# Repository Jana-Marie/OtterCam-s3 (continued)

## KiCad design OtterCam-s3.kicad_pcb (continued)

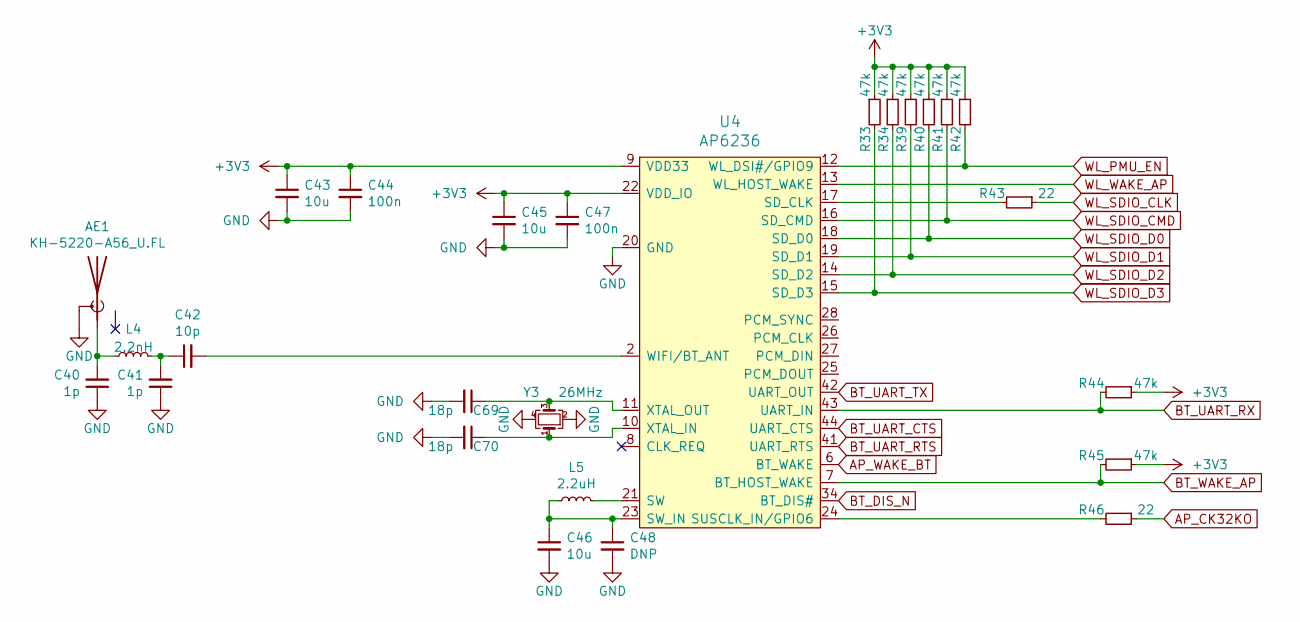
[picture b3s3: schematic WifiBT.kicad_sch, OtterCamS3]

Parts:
AE1: KH-5220-A56_U.FL; U.FL_Hirose_U.FL-R-SMT-1_Vertical
C40, C41: 1p; C_0402
C42: 10p; C_0402
C43, C45, C46: 10u; C_0603
C44, C47: 100n; C_0402
C48: DNP; C_0402
C69, C70: 18p; C_0402
L4: 2.2nH; L_0402
L5: 2.2uH; L_Taiyo-Yuden_MD-3030; LCSC C167747
R33, R34, R39, R40, R41, R42, R44, R45: 47k; R_0402
R43, R46: 22; R_0402
U4: AP6236; LGA_44_12x12mm_0.9mm
Y3: 26MHz; Oscillator_3225

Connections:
+3V3: C43.1, C44.1, C45.1, C47.1, R33.1, R34.1, R39.1, R40.1, R41.1, R42.1, R44.1, R45.1, U4.9 (VDD33), U4.22 (VDD_IO); also elsewhere on the board
AP_CK32KO: R46.1; also elsewhere on the board
AP_WAKE_BT: U4.6 (BT_WAKE); also elsewhere on the board
BT_DIS_N: U4.34 (BT_DIS#); also elsewhere on the board
BT_UART_CTS: U4.44 (UART_CTS); also elsewhere on the board
BT_UART_RTS: U4.41 (UART_RTS); also elsewhere on the board
BT_UART_RX: R44.2, U4.43 (UART_IN); also elsewhere on the board
BT_UART_TX: U4.42 (UART_OUT); also elsewhere on the board
BT_WAKE_AP: R45.2, U4.7 (BT_HOST_WAKE); also elsewhere on the board
GND: AE1.2 (Shield), C40.1, C41.1, C43.2, C44.2, C45.2, C46.2, C47.2, C48.2, C69.2, C70.2, U4.1 (GND), U4.20 (GND), U4.31 (GND), U4.33 (GND), U4.36 (GND), Y3.2, Y3.4; also elsewhere on the board
unnamed: AE1.1 (A), C40.2, L4.1
unnamed: C41.2, C42.1, L4.2
unnamed: C42.2, U4.2 (WIFI/BT_ANT)
unnamed: C46.1, C48.1, L5.1, U4.23 (SW_IN)
unnamed: C69.1, U4.11 (XTAL_OUT), Y3.3
unnamed: C70.1, U4.10 (XTAL_IN), Y3.1
unnamed: L5.2, U4.21 (SW)
unnamed: R43.2, U4.17 (SD_CLK)
unnamed: R46.2, U4.24 (SUSCLK_IN/GPIO6)
WL_PMU_EN: R42.2, U4.12 (WL_DSI#/GPIO9); also elsewhere on the board
WL_SDIO_CLK: R43.1; also elsewhere on the board
WL_SDIO_CMD: R41.2, U4.16 (SD_CMD); also elsewhere on the board
WL_SDIO_D0: R40.2, U4.18 (SD_D0); also elsewhere on the board
WL_SDIO_D1: R39.2, U4.19 (SD_D1); also elsewhere on the board
WL_SDIO_D2: R34.2, U4.14 (SD_D2); also elsewhere on the board
WL_SDIO_D3: R33.2, U4.15 (SD_D3); also elsewhere on the board
WL_WAKE_AP: U4.13 (WL_HOST_WAKE); also elsewhere on the board

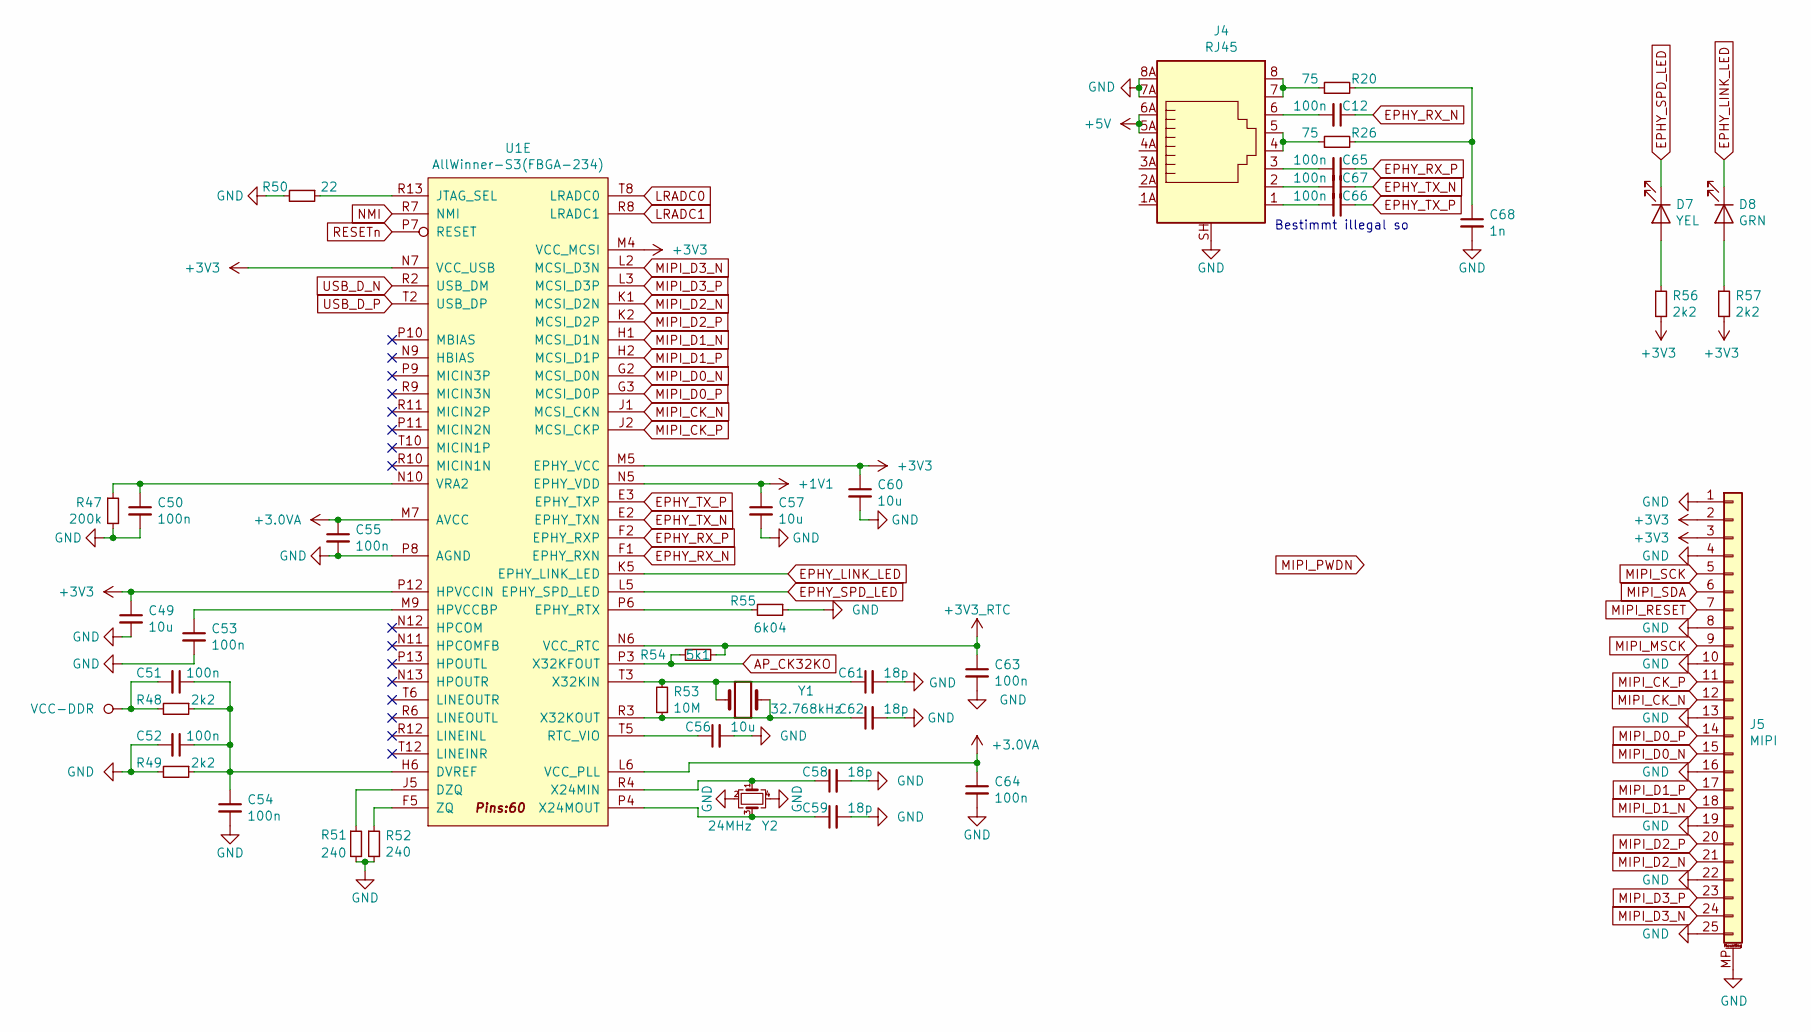
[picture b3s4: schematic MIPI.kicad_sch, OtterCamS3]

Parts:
C12, C65, C66, C67: 100n; C_0805
C49, C56, C57, C60: 10u; C_0603
C50, C51, C52, C53, C54, C55, C63, C64: 100n; C_0402
C58, C59, C61, C62: 18p; C_0402
C68: 1n; C_0805
D7: YEL; LED_0603_1608Metric_Castellated
D8: GRN; LED_0603_1608Metric_Castellated
J4: RJ45; 1-338088-3
J5: MIPI; FH35C-25S
R20, R26: 75; R_0402
R47: 200k; R_0402
R48, R49, R56, R57: 2k2; R_0402
R50: 22; R_0402
R51, R52: 240; R_0402
R53: 10M; R_0402
R54: 5k1; R_0402
R55: 6k04; R_0402
U1: AllWinner-S3(FBGA-234); FBGA-234(Pitch-0.65mm_Pad-0.3mm_11x11x1.08mm)
Y1: 32.768kHz; Crystal_SMD_3215-2Pin_3.2x1.5mm
Y2: 24MHz; Oscillator_3225

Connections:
+1V1: C57.1, U1.N5 (EPHY_VDD); also elsewhere on the board
+3.0VA: C55.1, C64.1, U1.L6 (VCC_PLL), U1.M7 (AVCC); also elsewhere on the board
+3.3V_RTC: C63.1, R54.2, U1.N6 (VCC_RTC); also elsewhere on the board
+3V3: C49.1, C60.1, J5.2, J5.3, R56.2, R57.2, U1.M4 (VCC_MCSI), U1.M5 (EPHY_VCC), U1.N7 (VCC_USB), U1.P12 (HPVCCIN); also elsewhere on the board
+5V: J4.5A, J4.6A; also elsewhere on the board
AP_CK32KO: R54.1, U1.P3 (X32KFOUT); also elsewhere on the board
EPHY_LINK_LED: D8.1 (K), U1.K5 (EPHY_LINK_LED)
EPHY_RX_N: C12.1, U1.F1 (EPHY_RXN)
EPHY_RX_P: C65.1, U1.F2 (EPHY_RXP)
EPHY_SPD_LED: D7.1 (K), U1.L5 (EPHY_SPD_LED)
EPHY_TX_N: C67.1, U1.E2 (EPHY_TXN)
EPHY_TX_P: C66.1, U1.E3 (EPHY_TXP)
GND: C49.2, C50.2, C52.2, C53.2, C54.2, C55.2, C56.2, C57.2, C58.2, C59.2, C60.2, C61.2, C62.2, C63.2, C64.2, C68.2, J4.7A, J4.8A, J4.SH, J5.1, J5.4, J5.8, J5.10, J5.13, J5.16, J5.19, J5.22, J5.25, J5.MP (MountPin), R47.2, R49.2, R50.2, R51.2, R52.2, R55.1, U1.P8 (AGND), Y2.2, Y2.4; also elsewhere on the board
LRADC0: U1.T8 (LRADC0)
LRADC1: U1.R8 (LRADC1)
MIPI_CK_N: J5.12, U1.J1 (MCSI_CKN)
MIPI_CK_P: J5.11, U1.J2 (MCSI_CKP)
MIPI_D0_N: J5.15, U1.G2 (MCSI_D0N)
MIPI_D0_P: J5.14, U1.G3 (MCSI_D0P)
MIPI_D1_N: J5.18, U1.H1 (MCSI_D1N)
MIPI_D1_P: J5.17, U1.H2 (MCSI_D1P)
MIPI_D2_N: J5.21, U1.K1 (MCSI_D2N)
MIPI_D2_P: J5.20, U1.K2 (MCSI_D2P)
MIPI_D3_N: J5.24, U1.L2 (MCSI_D3N)
MIPI_D3_P: J5.23, U1.L3 (MCSI_D3P)
MIPI_MSCK: J5.9; also elsewhere on the board
MIPI_RESET: J5.7; also elsewhere on the board
MIPI_SCK: J5.5; also elsewhere on the board
MIPI_SDA: J5.6; also elsewhere on the board
NMI: U1.R7 (NMI)
unnamed: C12.2, J4.6
unnamed: C50.1, R47.1, U1.N10 (VRA2)
unnamed: C51.1, C52.1, C54.1, R48.1, R49.1, U1.H6 (DVREF)
unnamed: C53.1, U1.M9 (HPVCCBP)
unnamed: C56.1, U1.T5 (RTC_VIO)
unnamed: C58.1, U1.R4 (X24MIN), Y2.1
unnamed: C59.1, U1.P4 (X24MOUT), Y2.3
unnamed: C61.1, R53.2, U1.T3 (X32KIN), Y1.1
unnamed: C62.1, R53.1, U1.R3 (X32KOUT), Y1.2
unnamed: C65.2, J4.3
unnamed: C66.2, J4.1
unnamed: C67.2, J4.2
unnamed: C68.1, R20.2, R26.2
unnamed: D7.2 (A), R56.1
unnamed: D8.2 (A), R57.1
unnamed: J4.4, J4.5, R26.1
unnamed: J4.7, J4.8, R20.1
unnamed: R50.1, U1.R13 (JTAG_SEL)
unnamed: R51.1, U1.J5 (DZQ)
unnamed: R52.1, U1.F5 (ZQ)
unnamed: R55.2, U1.P6 (EPHY_RTX)
RESETn: U1.P7 (RESET); also elsewhere on the board
USB_D_N: U1.R2 (USB_DM); also elsewhere on the board
USB_D_P: U1.T2 (USB_DP); also elsewhere on the board
VCC-DDR: C51.2, R48.2; also elsewhere on the board

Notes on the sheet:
Bestimmt illegal so

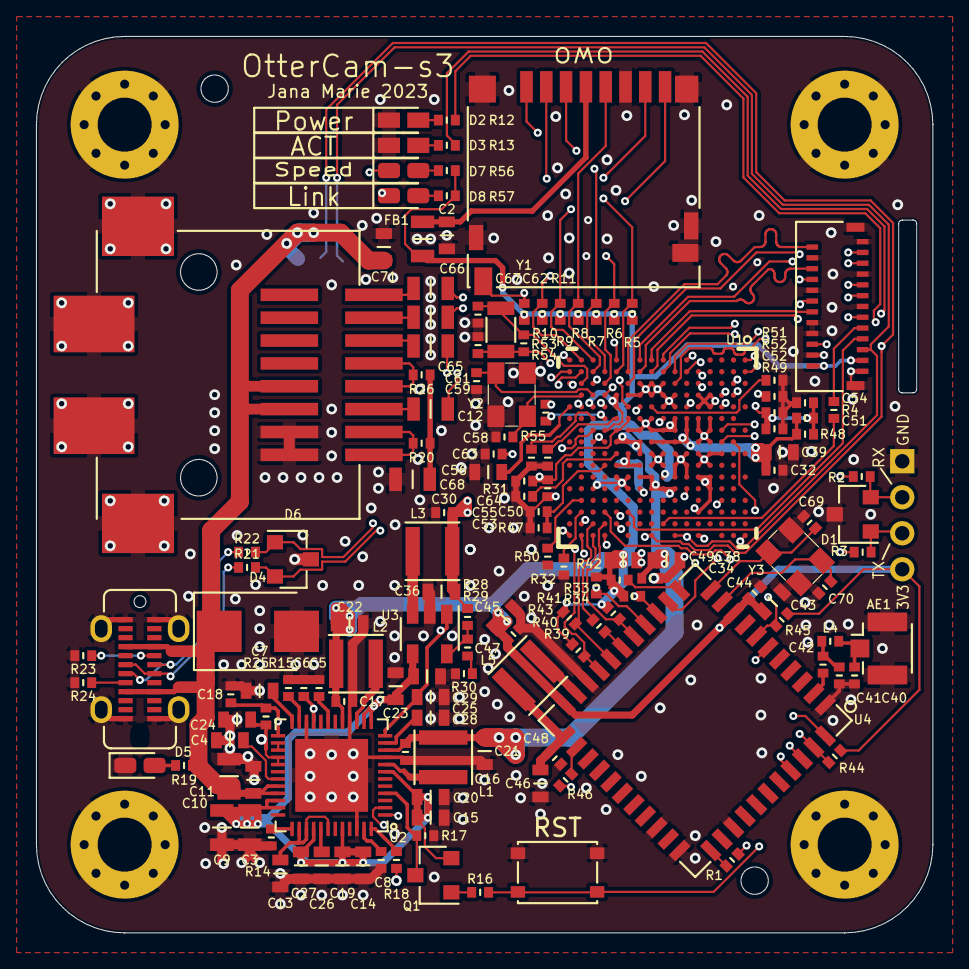
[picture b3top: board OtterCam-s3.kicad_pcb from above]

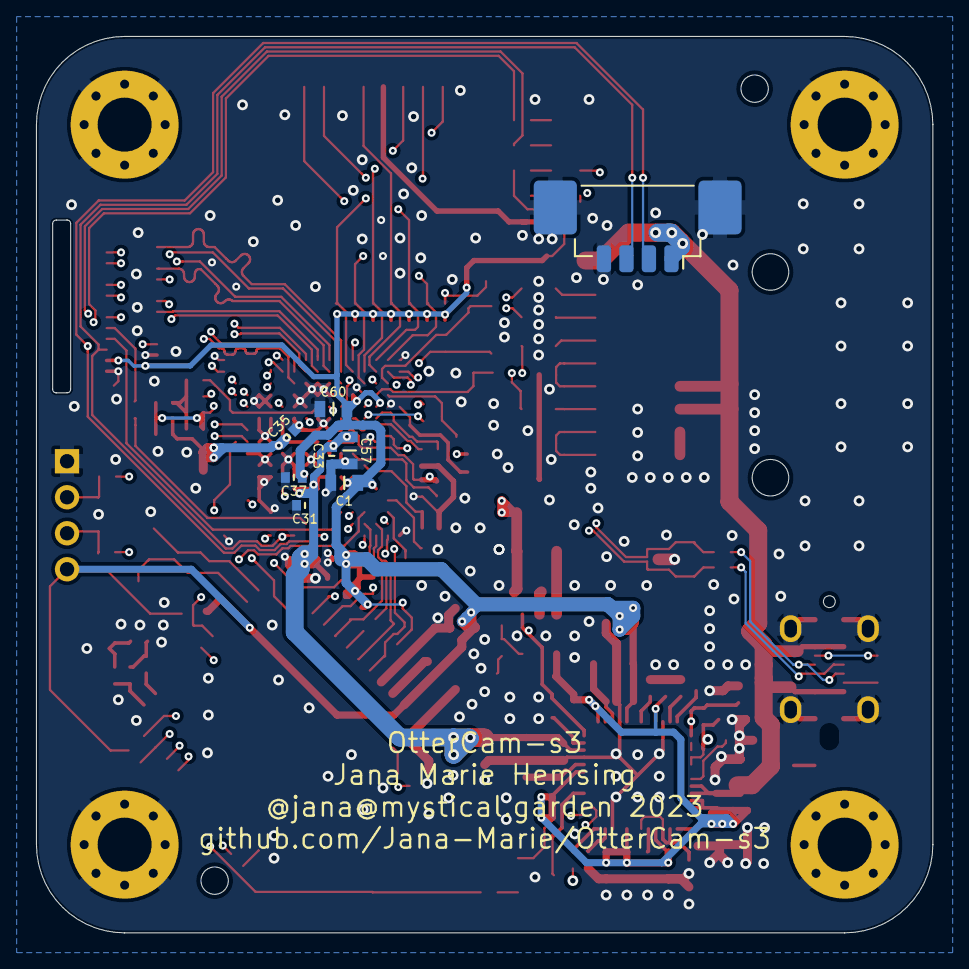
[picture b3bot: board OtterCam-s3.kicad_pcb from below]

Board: 4 copper layers, 49.8 x 49.8 mm, 159 parts (12 on the bottom side), 121 nets.

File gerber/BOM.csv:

Comment,Designator,Footprint,LCSC,
KH-5220-A56_U.FL,AE1,Connector_Coaxial:U.FL_Hirose_U.FL-R-SMT-1_Vertical,,
47u,"C10,C9,C3",otter:C_0805,C76636,
470n,C18,otter:C_0402,C47339,
10u,"C2,C1,C71,C15,C14,C21,C22,C20,C19,C23,C24,C25,C26,C27,C28,C4,C38,C39,C29,C36,C13,C11,C45,C43,C46,C57,C60,C56,C49",otter:C_0603,C19702 ,
100n,"C35,C37,C33,C34,C31,C32,C30,C5,C6,C17,C16,C47,C44,C55,C64,C63,C54,C51,C53,C52,C50",otter:C_0402,C1525,
1p,"C41,C40",otter:C_0402,C1550,
10p,C42,otter:C_0402,C32949,
DNP,C48,otter:C_0402,DNP,
100n,"C66,C67,C65,C12",otter:C_0805,C49678 ,
1n,C68,otter:C_0805,C46653,
2.2u,C7,otter:C_0603,C23630,
18p,"C70,C69,C58,C59,C61,C62",otter:C_0402,C1549,
1n,C8,otter:C_0402,C1523,
ESD5302F,"D1,D6",Package_TO_SOT_SMD:SOT-23,C32677,C239643
LED,D3,otter:LED_0603_1608Metric,C2286,
P6SMB6.8CA,D4,Diode_SMD:D_SMB,C78395,
LED,D5,LED_SMD:LED_0603_1608Metric_Castellated,C72043,
YEL,D7,LED_SMD:LED_0603_1608Metric_Castellated,C72038,
GRN,"D2,D8",LED_SMD:LED_0603_1608Metric_Castellated,C72043,
FERRET,FB1,otter:R_0805,C1017,
Fiducial,"FID1,FID2",otter:FID_1.52,DNP,
M3,"H1,H2,H3,H4",MountingHole:MountingHole_3mm_Pad_Via,DNP,
UART,J1,otter:PinHeader_1x04_P2.00mm_Vertical_nosilk_center,DNP,
SD,J2,Connector_Card:microSD_HC_Hirose_DM3D-SF,DNP,
USB,J3,otter:918-418K2022Y40004,DNP,
RJ45,J4,otter:1-338088-3,DNP,
MIPI,J5,otter:FH35C-25S,DNP,
LENS,J6,Connector_Molex:Molex_PicoBlade_53398-0471_1x04-1MP_P1.25mm_Vertical,DNP,
2.2uH,"L1,L2,L3,L5",Inductor_SMD:L_Taiyo-Yuden_MD-3030,C370424,C167747
2.2nH,L4,otter:L_0402,C27123,
DTA114YKA,Q1,Package_TO_SOT_SMD:SOT-23,C111713,
22,"R1,R31,R14,R43,R46,R50",otter:R_0402,C25077,
5k1,"R12,R13,R28,R32,R23,R24,R19,R54",otter:R_0402,C25905,
200k,"R15,R47",otter:R_0402,C25764 ,
DNP,R16,otter:R_0402,DNP,
2k2,"R17,R48,R49,R56,R57",otter:R_0402,C25879,
100,"R2,R3,R30",otter:R_0402,C25133,
75,"R26,R20",otter:R_0402,C25133,
3k3,R29,otter:R_0402,C25890,
0,"R4,R21,R22",otter:R_0402,C17168,
47k,"R5,R6,R7,R8,R9,R10,R11,R25,R18,R42,R41,R40,R39,R34,R33,R45,R44",otter:R_0402,C25792,
240,"R51,R52",otter:R_0402,C25094,
10M,R53,otter:R_0402,C26082,
6k04,R55,otter:R_0402,C25913,
RST,SW1,otter:SW_SPST_PTS810,DNP,
AllWinner-S3(FBGA-234),U1,otter:FBGA-234(Pitch-0.65mm_Pad-0.3mm_11x11x1.08mm),DNP,
AXP209(QFN-48),U2,otter:QFN-48-1EP_6x6mm_P0.4mm_EP4.05x4.05mm,C80525 ,
SY8089AAAC,U3,Package_TO_SOT_SMD:SOT-23-5,C78988,
AP6236,U4,otter:LGA_44_12x12mm_0.9mm,DNP,
32.768kHz,Y1,otter:Crystal_SMD_3215-2Pin_3.2x1.5mm,C32346,
24MHz,Y2,otter:Oscillator_3225,C89577,
26MHz,Y3,otter:Oscillator_3225,C136077 ,

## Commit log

2021-04-28 updated files
2021-04-28 removed old files
2021-04-28 added files
2021-04-28 routed mipi, eth and sdio
2021-04-28 routed all high speed signals
2021-05-02 mostly routed
2021-05-02 routing finished
2021-05-09 sensor board v1.0 mostly routed
2021-05-09 routing 100%
2021-05-09 new 3d files
2021-09-02 added images
2021-10-11 fixed MIPI pinout, added pullups, fixed silkscreen
2021-10-11 exported gerber, moved old gerber
2021-10-11 added all gerber
2021-10-11 renamed folder
2021-10-11 renamed lens folder
2021-10-11 added schematic print
2021-10-11 fixed silkscreen
2022-01-18 updated to kicad 6
2022-01-19 added license
2023-02-02 updated hw files
2023-02-02 updated gitignore
2023-02-02 added CAD readme
2023-02-02 added SCAD files
2023-02-02 added case stl files
2023-02-02 removed files
2023-02-02 removed binary files
2023-02-02 removed xml file
2023-02-02 updated schematic files
2023-02-02 updated project and board files
2023-02-02 updated sensor board
2023-02-02 updated lensmount
2023-02-02 removed binaries and old files
2023-02-02 updated pdfs
2023-02-02 updated c and cs mount
